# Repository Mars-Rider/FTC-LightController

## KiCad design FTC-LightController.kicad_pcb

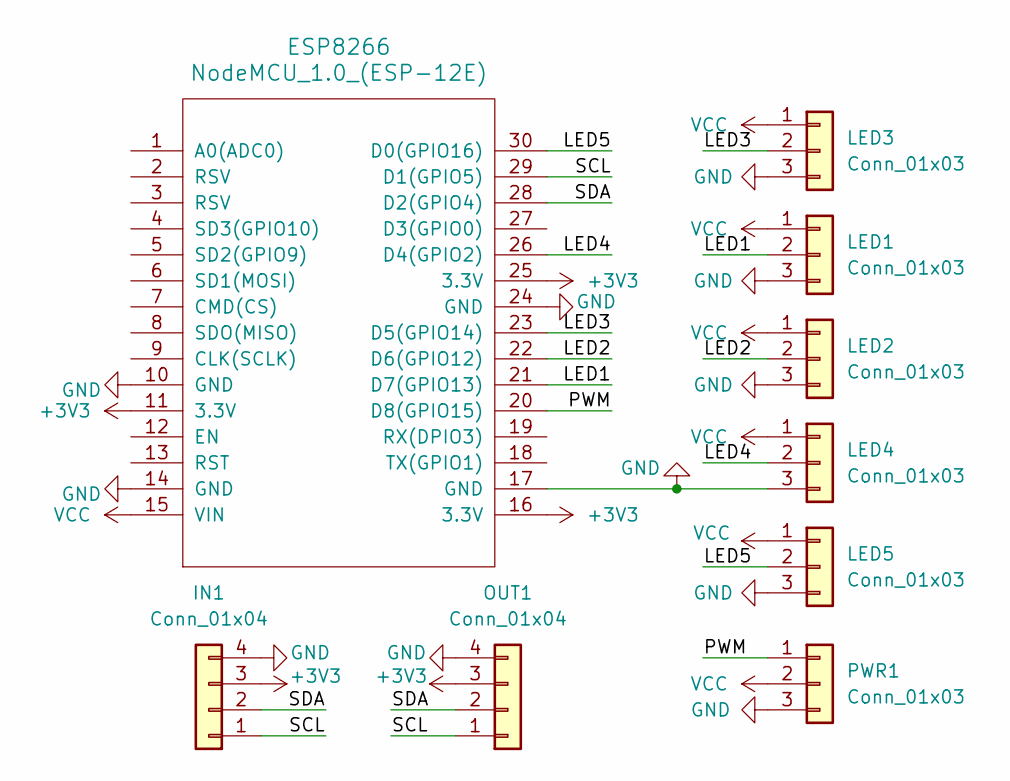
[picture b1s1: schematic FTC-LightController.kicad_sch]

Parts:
ESP8266: NodeMCU_1.0_(ESP-12E); ESP12F-Devkit-V3
IN1: Conn_01x04; JST_PH_B4B-PH-K_1x04_P2.00mm_Vertical
LED1, LED2, LED3, LED4, LED5: Conn_01x03; PinHeader_1x03_P2.54mm_Vertical
OUT1: Conn_01x04; JST_PH_B4B-PH-K_1x04_P2.00mm_Vertical
PWR1: Conn_01x03; PinHeader_1x03_P2.54mm_Vertical

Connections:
+3V3: ESP8266.11 (3.3V), ESP8266.16 (3.3V), ESP8266.25 (3.3V), IN1.3, OUT1.3
/LED1: ESP8266.21 (D7(GPIO13)), LED1.2
/LED2: ESP8266.22 (D6(GPIO12)), LED2.2
/LED3: ESP8266.23 (D5(GPIO14)), LED3.2
/LED4: ESP8266.26 (D4(GPIO2)), LED4.2
/LED5: ESP8266.30 (D0(GPIO16)), LED5.2
/PWM: ESP8266.20 (D8(GPIO15)), PWR1.1
/SCL: ESP8266.29 (D1(GPIO5)), IN1.1, OUT1.1
/SDA: ESP8266.28 (D2(GPIO4)), IN1.2, OUT1.2
GND: ESP8266.10 (GND), ESP8266.14 (GND), ESP8266.17 (GND), ESP8266.24 (GND), IN1.4, LED1.3, LED2.3, LED3.3, LED4.3, LED5.3, OUT1.4, PWR1.3
VCC: ESP8266.15 (VIN), LED1.1, LED2.1, LED3.1, LED4.1, LED5.1, PWR1.2

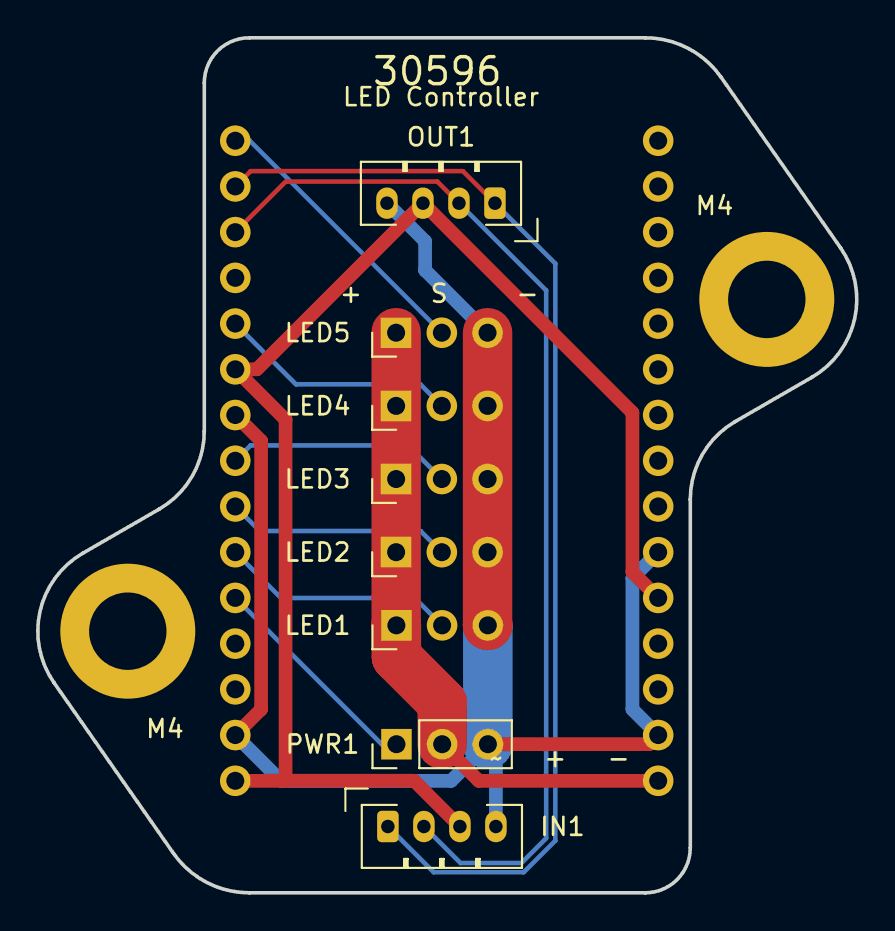
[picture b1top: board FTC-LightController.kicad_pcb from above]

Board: 2 copper layers, 45.5 x 47.5 mm, 11 parts (1 on the bottom side), 11 nets.

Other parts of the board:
M4, M4#2: MountingHole_4.3mm_M4_DIN965_Pad
